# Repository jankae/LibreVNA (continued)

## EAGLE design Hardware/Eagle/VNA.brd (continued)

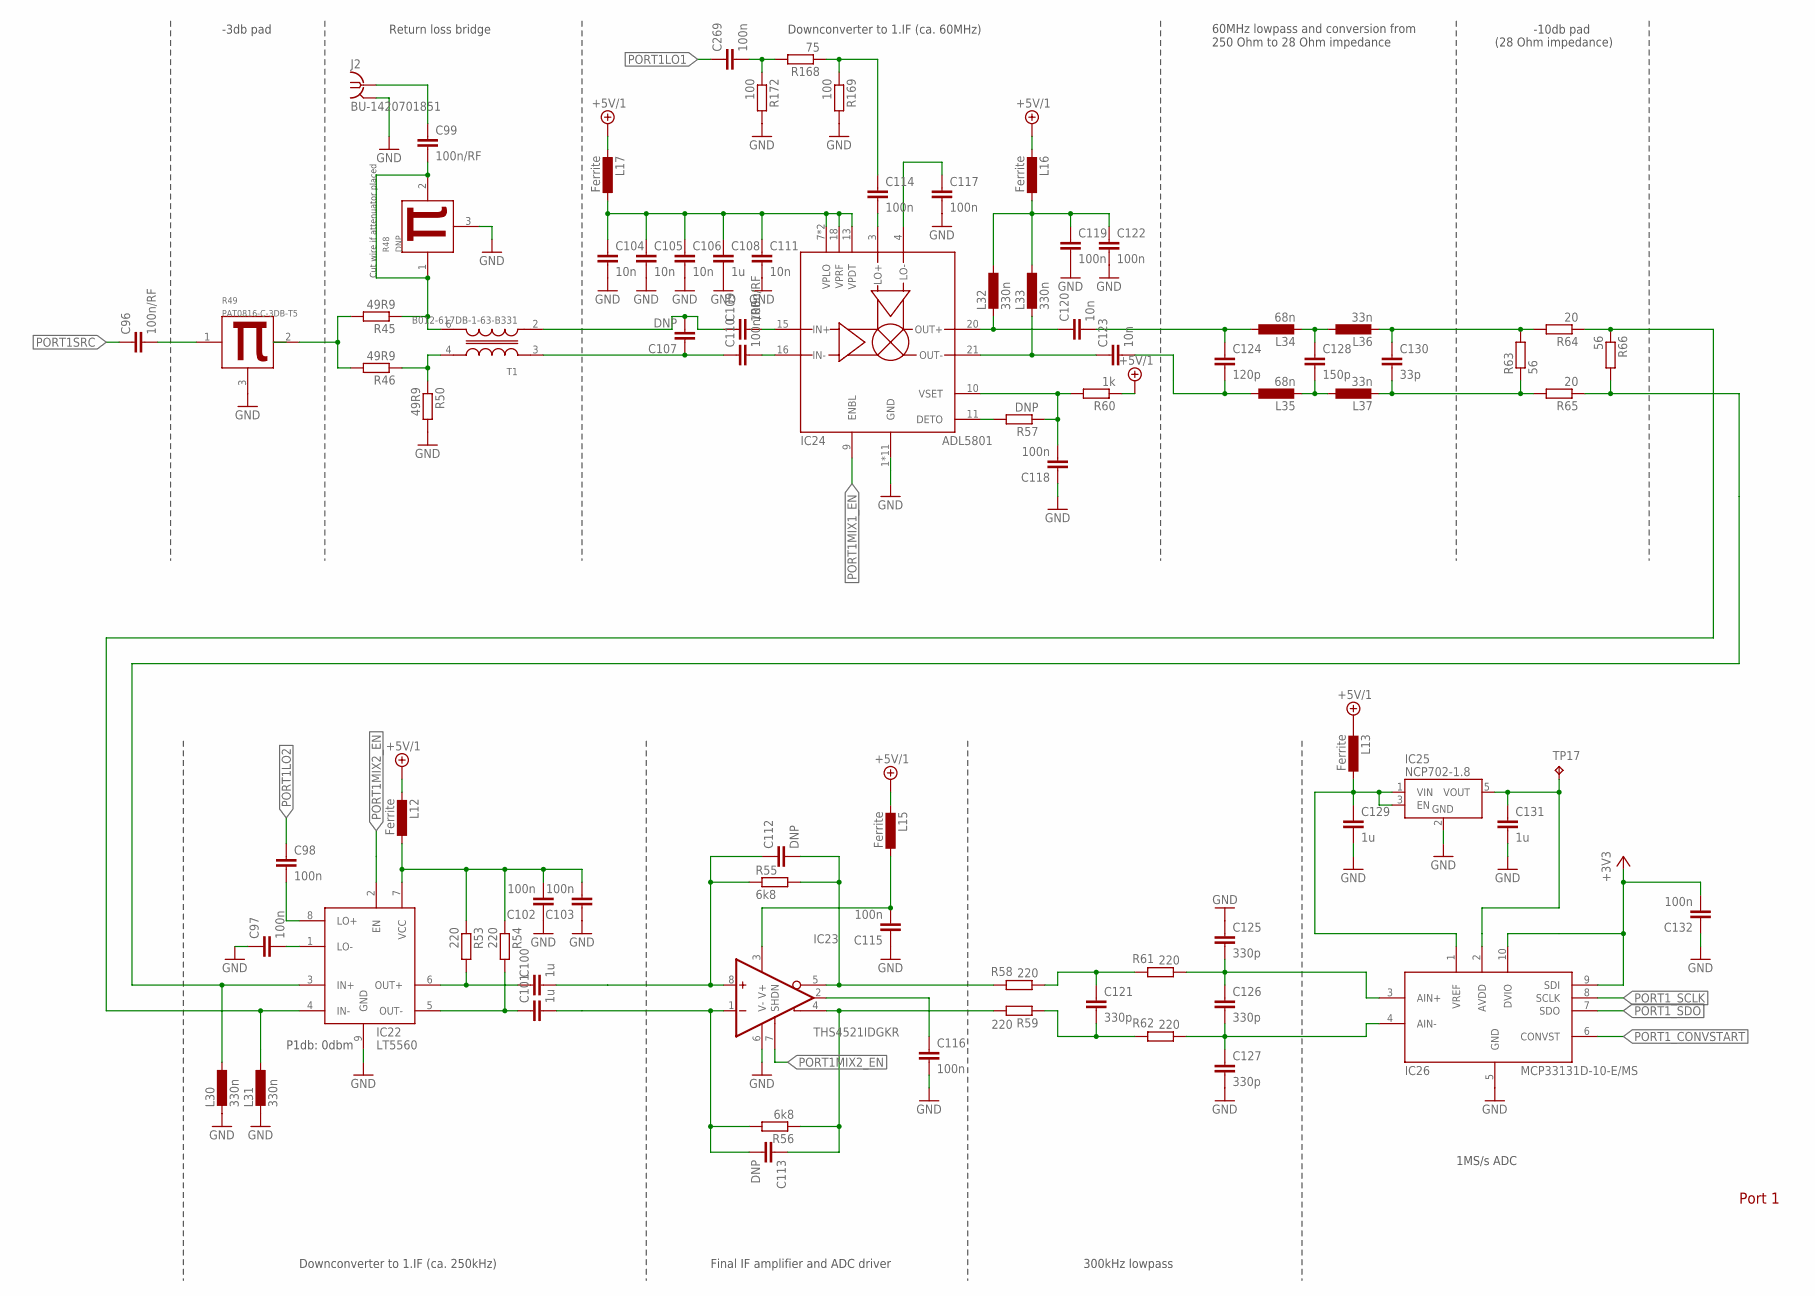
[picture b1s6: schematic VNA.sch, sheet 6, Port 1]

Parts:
C96, C99, C109, C110: 100n/RF; C0402
C97, C98, C102, C103, C114, C115, C116, C117, C118, C119, C122, C132, C269: 100n; C0402
C100, C101, C108, C129, C131: 1u; C0402
C104, C105, C106, C111, C120, C123: 10n; C0402
C107, C112, C113: DNP; C0402
C121, C125, C126, C127: 330p; C0402
C124: 120p; C0402
C128: 150p; C0402
C130: 33p; C0402
IC22: LT5560; SON50P300X300X80-9T165X238
IC23: THS4521IDGKR; SOP65P490X110-8N
IC24: ADL5801; QFN50P400X400X100-25T250N
IC25: NCP702-1.8; SOT95P240X110-5
IC26: MCP33131D-10-E/MS; SOP50P490X110-10N
J2: BU-1420701851
L12, L13, L15, L16, L17: Ferrite; R0402
L30, L31, L32, L33: 330n; L0402
L34, L35: 68n; L0402
L36, L37: 33n; L0402
R45, R46, R50: 49R9; R0402
R48: DNP; PAT0816
R49: PAT0816-C-3DB-T5; PAT0816
R53, R54, R58, R59, R61, R62: 220; R0402
R55, R56: 6k8; R0402
R57: DNP; R0402
R60: 1k; R0402
R63, R66: 56; R0402
R64, R65: 20; R0402
R168: 75; R0402
R169, R172: 100; R0402
T1: B012-617DB-1-63-B331; EASTEVER_BALUN
TP17: TPB1,27; B1,27

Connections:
+3V3: C132.2, IC26.9 (SDI), IC26.10 (DVIO); also elsewhere on the board
+5V/1: L12.2, L13.2, L15.2, L16.2, L17.2, R60.1; also elsewhere on the board
GND: C97.1, C102.1, C103.1, C104.2, C105.2, C106.2, C108.2, C111.2, C115.1, C116.2, C117.2, C118.1, C119.2, C122.2, C125.1, C127.2, C129.2, C131.2, C132.1, IC22.9 (GND), IC23.6 (V-), IC24.1 (GND), IC24.2 (GND), IC24.5 (GND), IC24.6 (GND), IC24.8 (GND), IC24.12 (GND), IC24.14 (GND), IC24.17 (GND), IC24.19 (GND), IC24.23 (GND), IC24.25 (GND), IC25.2 (GND), IC26.5 (GND), J2.G@1 (2), J2.G@2 (2), J2.G@3 (2), J2.G@4 (2), L30.2, L31.2, R48.3 (GND), R49.3 (GND), R50.2, R169.2, R172.2; also elsewhere on the board
unnamed: C96.2, R49.1 (IN)
unnamed: R45.2, R46.2, R49.2 (OUT)
unnamed: C120.2, C124.1, L34.1
unnamed: R46.1, R50.1, T1.4 (OUT+)
unnamed: C99.1, J2.1
unnamed: C109.2, IC24.15 (IN+)
unnamed: C110.2, IC24.16 (IN-)
unnamed: C107.1, C110.1, T1.3 (IN+)
unnamed: C107.2, C109.1, T1.2 (IN-)
unnamed: C117.1, IC24.4 (LO-)
unnamed: C114.2, IC24.3 (LO+)
unnamed: C125.2, C126.1, IC26.3 (AIN+), R61.1
unnamed: C120.1, IC24.20 (OUT+), L32.2
unnamed: C123.1, IC24.21 (OUT-), L33.2
unnamed: C123.2, C124.2, L35.1
unnamed: C128.2, L35.2, L37.1
unnamed: C98.2, IC22.8 (LO+)
unnamed: C118.2, IC24.10 (VSET), R57.1, R60.2
unnamed: C126.2, C127.1, IC26.4 (AIN-), R62.1
unnamed: C97.2, IC22.1 (LO-)
unnamed: C102.2, C103.2, IC22.7 (VCC), L12.1, R53.1, R54.1
unnamed: C100.1, IC22.6 (OUT+), R53.2
unnamed: C101.1, IC22.5 (OUT-), R54.2
unnamed: C113.1, IC23.4 (+OUT), R56.1, R59.2
unnamed: C112.2, IC23.5 (-OUT), R55.2, R58.2
unnamed: C128.1, L34.2, L36.1
unnamed: C130.1, L36.2, R63.2, R64.2
unnamed: C130.2, L37.2, R63.1, R65.2
unnamed: C101.2, C113.2, IC23.1 (-IN), R56.2
unnamed: C100.2, C112.1, IC23.8 (+IN), R55.1
unnamed: C131.1, IC25.5 (VOUT), IC26.2 (AVDD), TP17.TP
unnamed: IC22.4 (IN-), L31.1, R64.1, R66.1
unnamed: IC22.3 (IN+), L30.1, R65.1, R66.2
unnamed: IC24.11 (DETO), R57.2
unnamed: C129.1, IC25.1 (VIN), IC25.3 (EN), IC26.1 (VREF), L13.1
unnamed: C119.1, C122.1, L16.1, L32.1, L33.1
unnamed: C269.2, R168.2, R172.1
unnamed: C114.1, R168.1, R169.1
unnamed: C99.2, R45.1, R48.1 (IN), R48.2 (OUT), T1.6 (OUT-)
unnamed: C115.2, IC23.3 (V+), L15.1
unnamed: C104.1, C105.1, C106.1, C108.1, C111.1, IC24.7 (VPLO), IC24.13 (VPDT), IC24.18 (VPRF), IC24.24 (VPLO), L17.1
OUT+: C121.1, R58.1, R61.2
OUT-: C121.2, R59.1, R62.2
OUT_CM: C116.1, IC23.2 (VOCM)
PORT1LO1: C269.1; also elsewhere on the board
PORT1LO2: C98.1; also elsewhere on the board
PORT1MIX1_EN: IC24.9 (ENBL); also elsewhere on the board
PORT1MIX2_EN: IC22.2 (EN), IC23.7 (SHDN); also elsewhere on the board
PORT1SRC: C96.1; also elsewhere on the board
PORT1_CONVSTART: IC26.6 (CONVST); also elsewhere on the board
PORT1_SCLK: IC26.8 (SCLK); also elsewhere on the board
PORT1_SDO: IC26.7 (SDO); also elsewhere on the board

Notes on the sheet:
P1db: 0dbm
-3db pad
Return loss bridge
Downconverter to 1.IF (ca. 60MHz)
60MHz lowpass and conversion from 250 Ohm to 28 Ohm impedance
-10db pad
(28 Ohm impedance)
Downconverter to 1.IF (ca. 250kHz)
Final IF amplifier and ADC driver
300kHz lowpass
1MS/s ADC
Port 1
Cut wire if attenuator placed

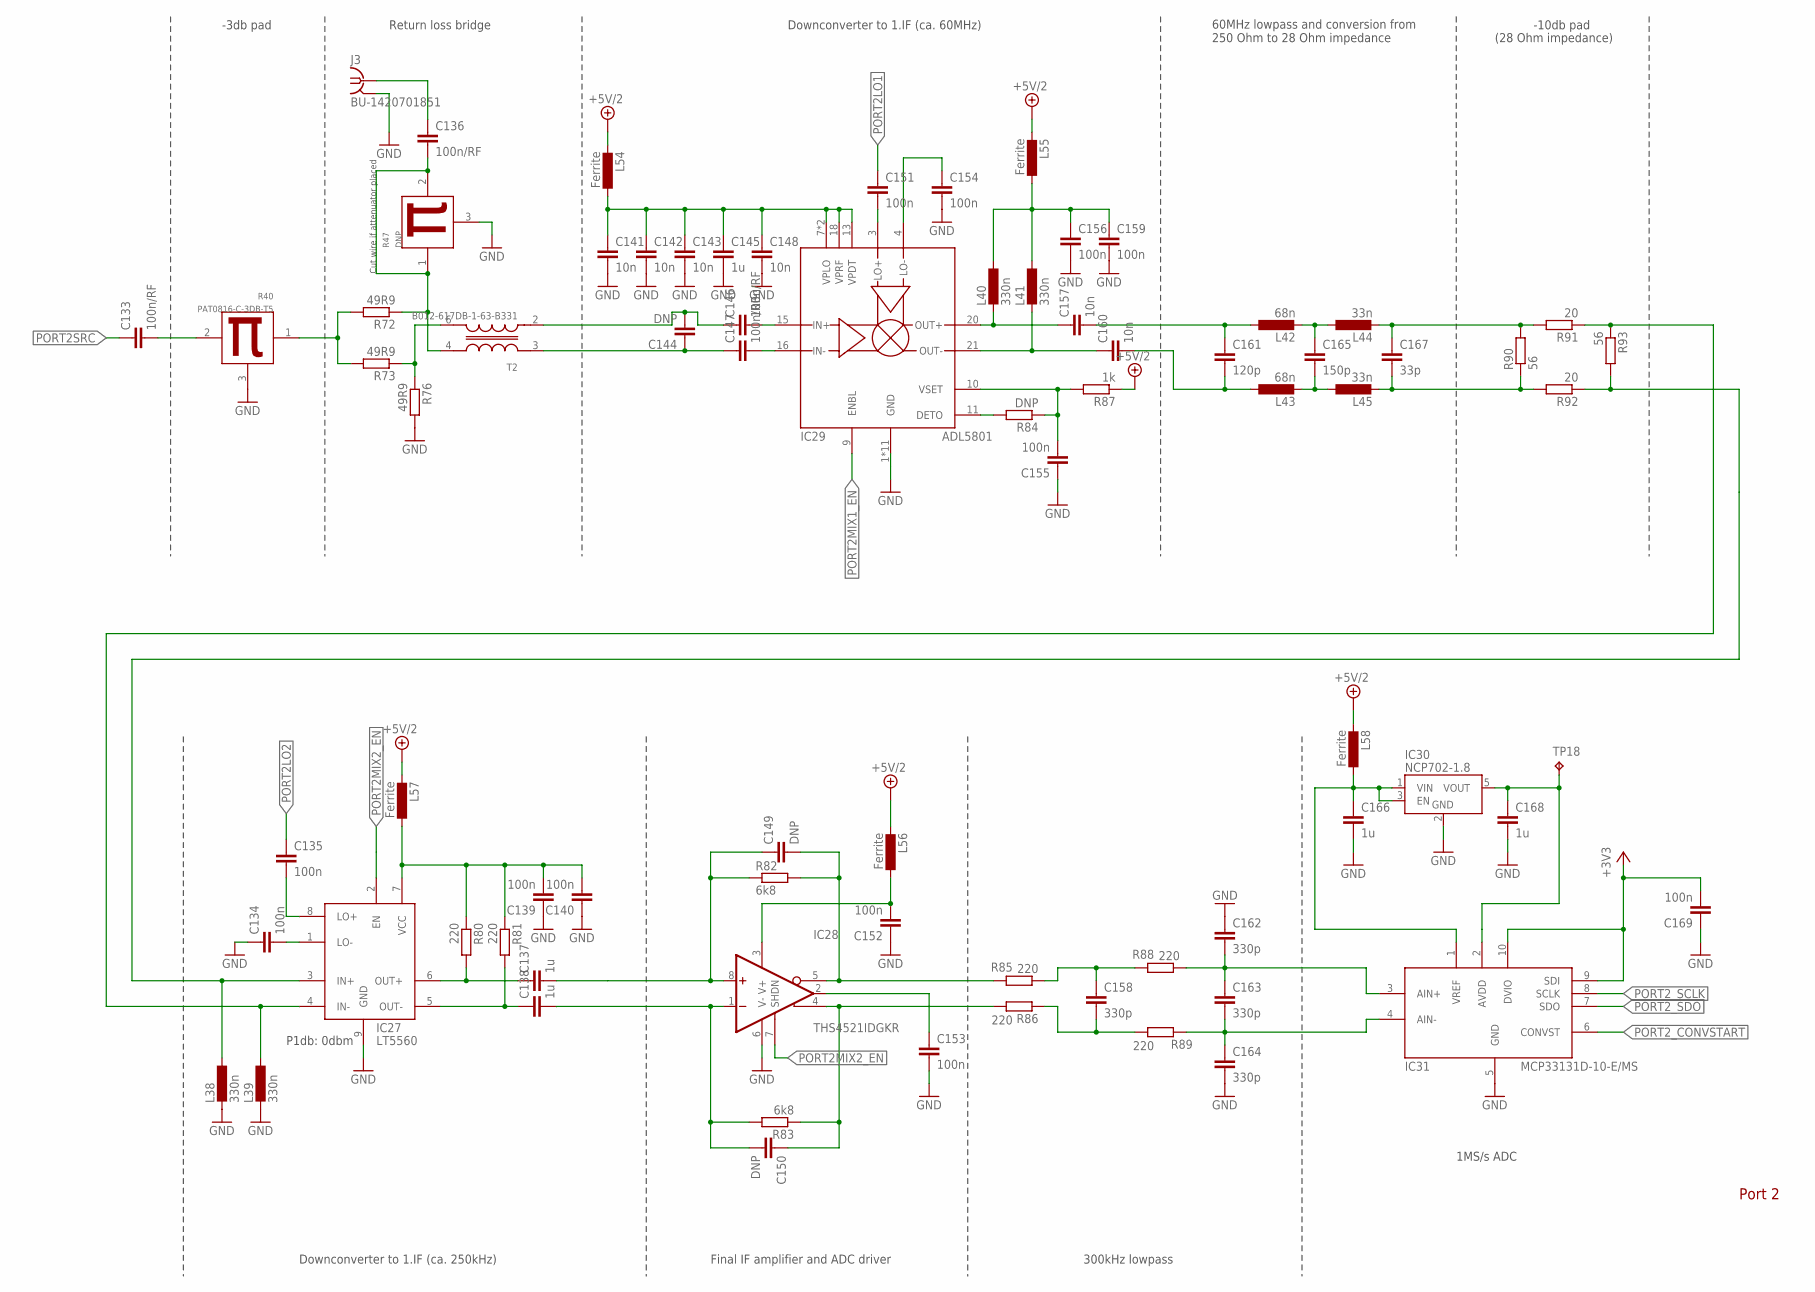
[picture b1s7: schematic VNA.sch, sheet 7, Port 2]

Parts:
C133, C136, C146, C147: 100n/RF; C0402
C134, C135, C139, C140, C151, C152, C153, C154, C155, C156, C159, C169: 100n; C0402
C137, C138, C145, C166, C168: 1u; C0402
C141, C142, C143, C148, C157, C160: 10n; C0402
C144, C149, C150: DNP; C0402
C158, C162, C163, C164: 330p; C0402
C161: 120p; C0402
C165: 150p; C0402
C167: 33p; C0402
IC27: LT5560; SON50P300X300X80-9T165X238
IC28: THS4521IDGKR; SOP65P490X110-8N
IC29: ADL5801; QFN50P400X400X100-25T250N
IC30: NCP702-1.8; SOT95P240X110-5
IC31: MCP33131D-10-E/MS; SOP50P490X110-10N
J3: BU-1420701851
L38, L39, L40, L41: 330n; L0402
L42, L43: 68n; L0402
L44, L45: 33n; L0402
L54, L55, L56, L57, L58: Ferrite; R0402
R40: PAT0816-C-3DB-T5; PAT0816
R47: DNP; PAT0816
R72, R73, R76: 49R9; R0402
R80, R81, R85, R86, R88, R89: 220; R0402
R82, R83: 6k8; R0402
R84: DNP; R0402
R87: 1k; R0402
R90, R93: 56; R0402
R91, R92: 20; R0402
T2: B012-617DB-1-63-B331; EASTEVER_BALUN
TP18: TPB1,27; B1,27

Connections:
+3V3: C169.2, IC31.9 (SDI), IC31.10 (DVIO); also elsewhere on the board
+5V/2: L54.2, L55.2, L56.2, L57.2, L58.2, R87.1; also elsewhere on the board
GND: C134.1, C139.1, C140.1, C141.2, C142.2, C143.2, C145.2, C148.2, C152.1, C153.2, C154.2, C155.1, C156.2, C159.2, C162.1, C164.2, C166.2, C168.2, C169.1, IC27.9 (GND), IC28.6 (V-), IC29.1 (GND), IC29.2 (GND), IC29.5 (GND), IC29.6 (GND), IC29.8 (GND), IC29.12 (GND), IC29.14 (GND), IC29.17 (GND), IC29.19 (GND), IC29.23 (GND), IC29.25 (GND), IC30.2 (GND), IC31.5 (GND), J3.G@1 (2), J3.G@2 (2), J3.G@3 (2), J3.G@4 (2), L38.2, L39.2, R40.3 (GND), R47.3 (GND), R76.2; also elsewhere on the board
unnamed: C136.2, R47.1 (IN), R47.2 (OUT), R72.1, T2.4 (OUT+)
unnamed: C133.2, R40.2 (OUT)
unnamed: R40.1 (IN), R72.2, R73.2
unnamed: IC27.3 (IN+), L38.1, R92.1, R93.2
unnamed: R73.1, R76.1, T2.6 (OUT-)
unnamed: C146.2, IC29.15 (IN+)
unnamed: C147.2, IC29.16 (IN-)
unnamed: C144.1, C147.1, T2.3 (IN+)
unnamed: C144.2, C146.1, T2.2 (IN-)
unnamed: C154.1, IC29.4 (LO-)
unnamed: C151.2, IC29.3 (LO+)
unnamed: C157.1, IC29.20 (OUT+), L40.2
unnamed: C160.1, IC29.21 (OUT-), L41.2
unnamed: C155.2, IC29.10 (VSET), R84.1, R87.2
unnamed: C134.2, IC27.1 (LO-)
unnamed: C137.1, IC27.6 (OUT+), R80.2
unnamed: C138.1, IC27.5 (OUT-), R81.2
unnamed: C150.1, IC28.4 (+OUT), R83.1, R86.2
unnamed: C149.2, IC28.5 (-OUT), R82.2, R85.2
unnamed: C157.2, C161.1, L42.1
unnamed: C160.2, C161.2, L43.1
unnamed: C165.2, L43.2, L45.1
unnamed: C165.1, L42.2, L44.1
unnamed: C135.2, IC27.8 (LO+)
unnamed: C162.2, C163.1, IC31.3 (AIN+), R88.1
unnamed: C163.2, C164.1, IC31.4 (AIN-), R89.1
unnamed: C167.1, L44.2, R90.2, R91.2
unnamed: C167.2, L45.2, R90.1, R92.2
unnamed: C138.2, C150.2, IC28.1 (-IN), R83.2
unnamed: C137.2, C149.1, IC28.8 (+IN), R82.1
unnamed: C168.1, IC30.5 (VOUT), IC31.2 (AVDD), TP18.TP
unnamed: IC27.4 (IN-), L39.1, R91.1, R93.1
unnamed: IC29.11 (DETO), R84.2
unnamed: C136.1, J3.1
unnamed: C141.1, C142.1, C143.1, C145.1, C148.1, IC29.7 (VPLO), IC29.13 (VPDT), IC29.18 (VPRF), IC29.24 (VPLO), L54.1
unnamed: C156.1, C159.1, L40.1, L41.1, L55.1
unnamed: C152.2, IC28.3 (V+), L56.1
unnamed: C139.2, C140.2, IC27.7 (VCC), L57.1, R80.1, R81.1
unnamed: C166.1, IC30.1 (VIN), IC30.3 (EN), IC31.1 (VREF), L58.1
OUT+1: C158.1, R85.1, R88.2
OUT-1: C158.2, R86.1, R89.2
OUT_CM1: C153.1, IC28.2 (VOCM)
PORT2LO1: C151.1; also elsewhere on the board
PORT2LO2: C135.1; also elsewhere on the board
PORT2MIX1_EN: IC29.9 (ENBL); also elsewhere on the board
PORT2MIX2_EN: IC27.2 (EN), IC28.7 (SHDN); also elsewhere on the board
PORT2SRC: C133.1; also elsewhere on the board
PORT2_CONVSTART: IC31.6 (CONVST); also elsewhere on the board
PORT2_SCLK: IC31.8 (SCLK); also elsewhere on the board
PORT2_SDO: IC31.7 (SDO); also elsewhere on the board

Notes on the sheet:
P1db: 0dbm
-3db pad
Return loss bridge
Downconverter to 1.IF (ca. 60MHz)
60MHz lowpass and conversion from 250 Ohm to 28 Ohm impedance
-10db pad
(28 Ohm impedance)
Downconverter to 1.IF (ca. 250kHz)
Final IF amplifier and ADC driver
300kHz lowpass
1MS/s ADC
Port 2
Cut wire if attenuator placed

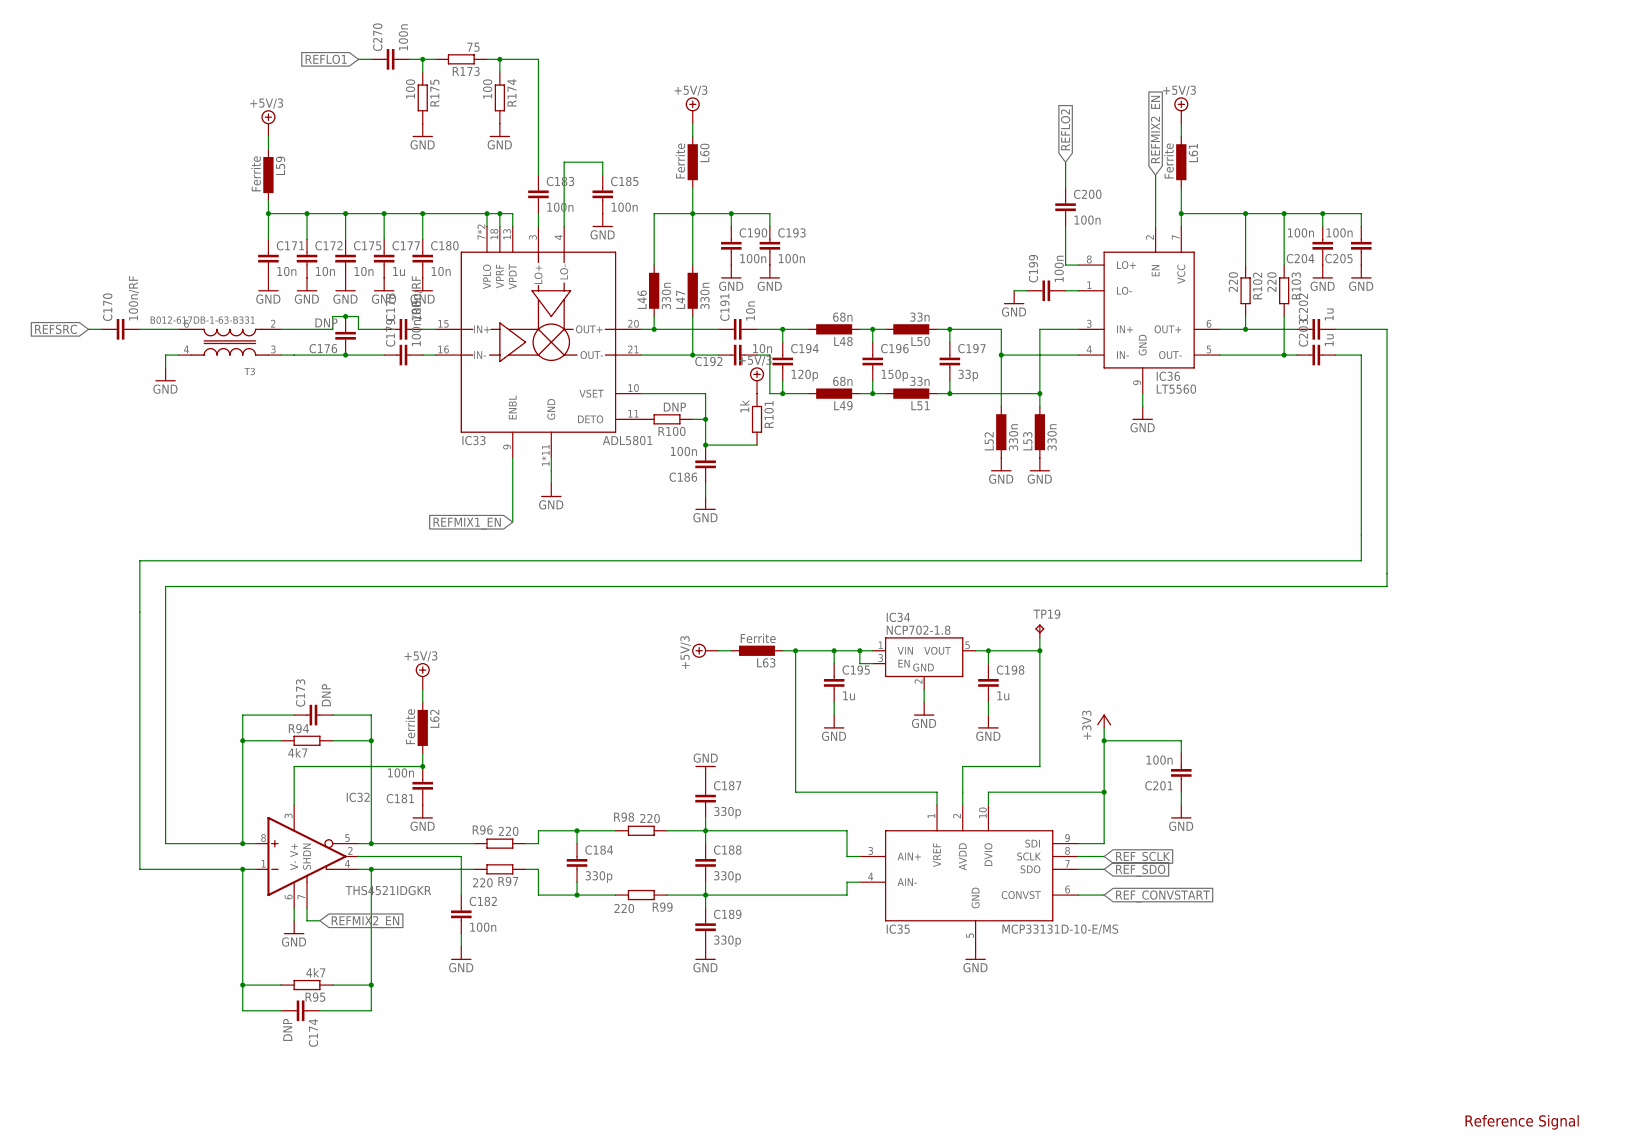
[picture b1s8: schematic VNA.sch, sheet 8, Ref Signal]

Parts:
C170, C178, C179: 100n/RF; C0402
C171, C172, C175, C180, C191, C192: 10n; C0402
C173, C174, C176: DNP; C0402
C177, C195, C198, C202, C203: 1u; C0402
C181, C182, C183, C185, C186, C190, C193, C199, C200, C201, C204, C205, C270: 100n; C0402
C184, C187, C188, C189: 330p; C0402
C194: 120p; C0402
C196: 150p; C0402
C197: 33p; C0402
IC32: THS4521IDGKR; SOP65P490X110-8N
IC33: ADL5801; QFN50P400X400X100-25T250N
IC34: NCP702-1.8; SOT95P240X110-5
IC35: MCP33131D-10-E/MS; SOP50P490X110-10N
IC36: LT5560; SON50P300X300X80-9T165X238
L46, L47, L52, L53: 330n; L0402
L48, L49: 68n; L0402
L50, L51: 33n; L0402
L59, L60, L61, L62, L63: Ferrite; R0402
R94, R95: 4k7; R0402
R96, R97, R98, R99, R102, R103: 220; R0402
R100: DNP; R0402
R101: 1k; R0402
R173: 75; R0402
R174, R175: 100; R0402
T3: B012-617DB-1-63-B331; EASTEVER_BALUN
TP19: TPB1,27; B1,27

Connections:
+3V3: C201.2, IC35.9 (SDI), IC35.10 (DVIO); also elsewhere on the board
+5V/3: L59.2, L60.2, L61.2, L62.2, L63.1, R101.1; also elsewhere on the board
GND: C171.2, C172.2, C175.2, C177.2, C180.2, C181.1, C182.2, C185.2, C186.1, C187.1, C189.2, C190.2, C193.2, C195.2, C198.2, C199.1, C201.1, C204.1, C205.1, IC32.6 (V-), IC33.1 (GND), IC33.2 (GND), IC33.5 (GND), IC33.6 (GND), IC33.8 (GND), IC33.12 (GND), IC33.14 (GND), IC33.17 (GND), IC33.19 (GND), IC33.23 (GND), IC33.25 (GND), IC34.2 (GND), IC35.5 (GND), IC36.9 (GND), L52.2, L53.2, R174.2, R175.2, T3.4 (OUT+); also elsewhere on the board
unnamed: C170.2, T3.6 (OUT-)
unnamed: C178.2, IC33.15 (IN+)
unnamed: C179.2, IC33.16 (IN-)
unnamed: C176.1, C179.1, T3.3 (IN+)
unnamed: C176.2, C178.1, T3.2 (IN-)
unnamed: C185.1, IC33.4 (LO-)
unnamed: C183.2, IC33.3 (LO+)
unnamed: C191.1, IC33.20 (OUT+), L46.2
unnamed: C192.1, IC33.21 (OUT-), L47.2
unnamed: C186.2, IC33.10 (VSET), R100.1, R101.2
unnamed: C199.2, IC36.1 (LO-)
unnamed: C202.1, IC36.6 (OUT+), R102.2
unnamed: C203.1, IC36.5 (OUT-), R103.2
unnamed: C173.1, C202.2, IC32.8 (+IN), R94.1
unnamed: C174.2, C203.2, IC32.1 (-IN), R95.2
unnamed: C174.1, IC32.4 (+OUT), R95.1, R97.2
unnamed: C173.2, IC32.5 (-OUT), R94.2, R96.2
unnamed: C191.2, C194.1, L48.1
unnamed: C192.2, C194.2, L49.1
unnamed: C196.2, L49.2, L51.1
unnamed: C196.1, L48.2, L50.1
unnamed: C197.1, IC36.4 (IN-), L50.2, L52.1
unnamed: C197.2, IC36.3 (IN+), L51.2, L53.1
unnamed: C200.2, IC36.8 (LO+)
unnamed: C187.2, C188.1, IC35.3 (AIN+), R98.1
unnamed: C188.2, C189.1, IC35.4 (AIN-), R99.1
unnamed: C198.1, IC34.5 (VOUT), IC35.2 (AVDD), TP19.TP
unnamed: IC33.11 (DETO), R100.2
unnamed: C270.2, R173.2, R175.1
unnamed: C183.1, R173.1, R174.1
unnamed: C171.1, C172.1, C175.1, C177.1, C180.1, IC33.7 (VPLO), IC33.13 (VPDT), IC33.18 (VPRF), IC33.24 (VPLO), L59.1
unnamed: C190.1, C193.1, L46.1, L47.1, L60.1
unnamed: C204.2, C205.2, IC36.7 (VCC), L61.1, R102.1, R103.1
unnamed: C181.2, IC32.3 (V+), L62.1
unnamed: C195.1, IC34.1 (VIN), IC34.3 (EN), IC35.1 (VREF), L63.2
OUT+2: C184.1, R96.1, R98.2
OUT-2: C184.2, R97.1, R99.2
OUT_CM2: C182.1, IC32.2 (VOCM)
REFLO1: C270.1; also elsewhere on the board
REFLO2: C200.1; also elsewhere on the board
REFMIX1_EN: IC33.9 (ENBL); also elsewhere on the board
REFMIX2_EN: IC32.7 (SHDN), IC36.2 (EN); also elsewhere on the board
REFSRC: C170.1; also elsewhere on the board
REF_CONVSTART: IC35.6 (CONVST); also elsewhere on the board
REF_SCLK: IC35.8 (SCLK); also elsewhere on the board
REF_SDO: IC35.7 (SDO); also elsewhere on the board

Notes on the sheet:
Reference Signal

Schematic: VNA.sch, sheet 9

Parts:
C206, C207, C208, C209, C210, C211, C212, C213, C214, C215, C216, C217, C218, C219, C220, C221, C222: 100n; C0402
C231, C232, C233, C234: 100p; C0402
IC37: STM32G431CB; QFN50P700X700X60-49T560N
J4: TYPE-C16P(073); TYPE-C16P
JP1: DNP; 1X10/90
LED1: Red; CHIPLED_0603
R104, R105, R106, R107, R108, R109, R110: 0; R0402
R111, R112, R113, R114, R115: DNP; R0402
R116, R117, R121, R122, R127, R128, R129, R147, R148: 10k; R0402
R118, R119, R123, R124, R126: 20; R0402
R120: 330; R0402
U1: W25Q16BVSN; SO08
U2: 6SLX9TQG144; TQ144

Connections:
+3V3: C206.1, C207.1, C208.1, C209.1, C210.1, C212.1, C214.1, C216.1, C218.1, C220.1, C221.1, C222.1, IC37.1 (VBAT), IC37.20 (VREF+), IC37.21 (VDDA), IC37.23 (VDD), IC37.35 (VDD), IC37.48 (VDD), JP1.5, LED1.A, R108.1, R116.2, R117.2, R121.2, R127.2, R128.2, R129.2, U1.3 (!WP!), U1.7 (!HOLD!), U1.8 (VCC), U2.P20 (VCCAUX), U2.P36 (VCCAUX), U2.P42 (VCCO_2), U2.P53 (VCCAUX), U2.P63 (VCCO_2), U2.P69 (IO_L1N_M0_CMPMISO_2), U2.P90 (VCCAUX), U2.P129 (VCCAUX); also elsewhere on the board
EN_6V: IC37.25 (PB12); also elsewhere on the board
FPGA_CCLK: R109.2, R111.2, U2.P70 (IO_L1P_CCLK_2)
FPGA_CLK: R126.1; also elsewhere on the board
FPGA_CSO_B: R114.2, U2.P38 (IO_L65N_CSO_B_2)
FPGA_DIN: R110.2, R113.2, U2.P65 (IO_L3P_D0_DIN_MISO_MISO1_2)
FPGA_DONE: IC37.47 (PB9), R129.1, U2.P71 (DONE_2)
FPGA_INIT_B: IC37.6 (PF1-OSC_OUT), R128.1, U2.P39 (IO_L65P_INIT_B_2)
FPGA_M1: R108.2, R115.1, U2.P60 (IO_L13P_M1_2)
FPGA_MOSI: R112.2, U2.P64 (IO_L3N_MOSI_CSI_B_MISO0_2)
FPGA_PROGRAM_B: IC37.19 (PB2), R127.1, U2.P37 (PROGRAM_B_2)
FPGA_RESET: IC37.45 (PB7), U2.P72 (CMPCS_B_2)
GND: C206.2, C207.2, C208.2, C209.2, C210.2, C211.2, C212.2, C213.2, C214.2, C215.2, C216.2, C217.2, C218.2, C219.2, C220.2, C221.2, C222.2, C231.2, C232.2, C233.2, C234.2, IC37.46 (PB8-BOOT0), IC37.49 (GND), J4.1 (GND), J4.12 (GND), J4.M1 (CASE), J4.M2 (CASE), J4.M3 (CASE), J4.M4 (CASE), JP1.7, R115.2, R122.1, U1.4 (GND), U2.P3 (GND), U2.P13 (GND), U2.P25 (GND), U2.P49 (GND), U2.P54 (GND), U2.P68 (GND), U2.P73 (SUSPEND), U2.P77 (GND), U2.P91 (GND), U2.P96 (GND), U2.P108 (GND), U2.P113 (GND), U2.P130 (GND), U2.P136 (GND); also elsewhere on the board
LO1_CE: U2.P45 (IO_L49N_D4_2); also elsewhere on the board
LO1_CLK: U2.P48 (IO_L48P_D7_2); also elsewhere on the board
LO1_LD: U2.P56 (IO_L30P_GCLK1_D13_2); also elsewhere on the board
LO1_LE: U2.P46 (IO_L49P_D3_2); also elsewhere on the board
LO1_MOSI: U2.P47 (IO_L48N_RDWR_B_VREF_2); also elsewhere on the board
LO1_MUX: U2.P51 (IO_L31P_GCLK31_D14_2); also elsewhere on the board
LO1_RF_EN: U2.P55 (IO_L30N_GCLK0_USERCCLK_2); also elsewhere on the board
MCU_AUX1: IC37.9 (PA1); also elsewhere on the board
MCU_AUX2: IC37.10 (PA2); also elsewhere on the board
MCU_AUX3: IC37.11 (PA3); also elsewhere on the board
MCU_FLASH_CS: IC37.17 (PB0), R107.1
MCU_FPGA_CCLK: IC37.26 (PB13), R109.1
MCU_FPGA_DIN: IC37.28 (PB15), R110.1
MCU_FPGA_NSS: IC37.12 (PA4), U2.P67 (IO_L2P_CMPCLK_2)
MCU_FPGA_UNUSED1: IC37.43 (PB5); also elsewhere on the board
MCU_FPGA_UNUSED2: IC37.41 (PB3); also elsewhere on the board
MCU_FPGA_UNUSED3: IC37.40 (PC11); also elsewhere on the board
MCU_INTR: IC37.18 (PB1), U2.P59 (IO_L13N_D10_2)
MCU_MISO: IC37.14 (PA6), R106.1, U2.P62 (IO_L12P_D1_MISO2_2)
MCU_MOSI: IC37.15 (PA7), R105.1, U2.P61 (IO_L12N_D2_MISO3_2)
MCU_SCK: IC37.13 (PA5), R104.1, U2.P66 (IO_L2N_CMPMOSI_2)
unnamed: C232.1, R122.2, R147.1, U2.P57 (IO_L14N_D12_2)
unnamed: J4.6 (D+1), J4.8 (D+2), R119.2
unnamed: IC37.33 (PA11), R118.2
unnamed: IC37.34 (PA12), R119.1
unnamed: J4.5 (D-2), J4.7 (D-1), R118.1
unnamed: LED1.C, R120.1
unnamed: IC37.38 (PA15), R120.2
unnamed: R104.2, R111.1, U1.6 (CLK)
unnamed: R126.2, U2.P50 (IO_L31N_GCLK30_D15_2)
unnamed: R124.2, U2.P41 (IO_L64P_D8_2)
unnamed: R123.2, U2.P43 (IO_L62N_D6_2)
unnamed: IC37.31 (PA9), IC37.44 (PB6), J4.4 (CC1)
unnamed: IC37.32 (PA10), IC37.42 (PB4), J4.10 (CC2)
unnamed: R105.2, R112.1, U1.5 (DI)
unnamed: R106.2, R113.1, U1.2 (DO)
unnamed: R107.2, R114.1, U1.1 (!CS!)
unnamed: C234.1, R121.1, R148.2, U2.P58 (IO_L14P_D11_2)
NRST: IC37.7 (PG10-NRST), JP1.9
PORT2MIX1_EN: C233.1, R148.1; also elsewhere on the board
PORT2MIX2_EN: C231.1, R147.2; also elsewhere on the board
PORT2SWITCH: U2.P40 (IO_L64N_D9_2); also elsewhere on the board
PORT2_CONVSTART: U2.P44 (IO_L62P_D5_2); also elsewhere on the board
PORT2_SCLK: R124.1; also elsewhere on the board
PORT2_SDO: R123.1; also elsewhere on the board
SCL: IC37.16 (PC4), R116.1; also elsewhere on the board
SDA: IC37.30 (PA8), R117.1; also elsewhere on the board
SWCLK: IC37.37 (PA14), JP1.6
SWDIO: IC37.36 (PA13), JP1.8
TCK: JP1.1, U2.P109 (TCK)
TDI: JP1.3, U2.P110 (TDI)
TDO: JP1.2, U2.P106 (TDO)
TMS: JP1.4, U2.P107 (TMS)
UART_TX: IC37.39 (PC10), JP1.10
USB_POWER: J4.2 (VBUS), J4.11 (VBUS); also elsewhere on the board
VCCINT: C211.1, C213.1, C215.1, C217.1, C219.1, U2.P19 (VCCINT), U2.P28 (VCCINT), U2.P52 (VCCINT), U2.P89 (VCCINT), U2.P128 (VCCINT); also elsewhere on the board

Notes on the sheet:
FPGA + MCU Connections
Place resistors for FPGA master configuration
Place resistors for FPGA slave configuration

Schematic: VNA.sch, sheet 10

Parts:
C223, C224, C225, C226, C227, C228, C229, C230: 100p; C0402
JP2: DNP; 2X10
LED2, LED6, LED7, LED8, LED9, LED10: Green; CHIPLED_0603
LED3, LED4, LED5: Red; CHIPLED_0603
R130, R131, R132, R133, R143, R144, R145, R146: 10k; R0402
R134, R135, R136, R137, R138, R139, R140, R141, R142: 330; R0402
U2: 6SLX9TQG144; TQ144

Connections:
+3V3: JP2.1, LED2.A, LED3.A, LED4.A, LED5.A, LED6.A, LED7.A, LED8.A, LED9.A, LED10.A, R130.2, R132.2, U2.P4 (VCCO_3), U2.P18 (VCCO_3), U2.P31 (VCCO_3), U2.P76 (VCCO_1), U2.P86 (VCCO_1), U2.P103 (VCCO_1), U2.P122 (VCCO_0), U2.P125 (VCCO_0), U2.P135 (VCCO_0); also elsewhere on the board
AMP_PWDN: U2.P8 (IO_L51P_3); also elsewhere on the board
ATT_D0: U2.P16 (IO_L43N_GCLK22_IRDY2_3); also elsewhere on the board
ATT_D1: U2.P15 (IO_L44P_GCLK21_3); also elsewhere on the board
ATT_D2: U2.P14 (IO_L44N_GCLK20_3); also elsewhere on the board
ATT_D3: U2.P12 (IO_L49P_3); also elsewhere on the board
ATT_D4: U2.P11 (IO_L49N_3); also elsewhere on the board
ATT_D5: U2.P10 (IO_L50P_3); also elsewhere on the board
ATT_D6: U2.P9 (IO_L50N_3); also elsewhere on the board
FILT_IN_C1: U2.P26 (IO_L37N_3); also elsewhere on the board
FILT_IN_C2: U2.P24 (IO_L41P_GCLK27_3); also elsewhere on the board
FILT_OUT_C1: U2.P22 (IO_L42P_GCLK25_TRDY2_3); also elsewhere on the board
FILT_OUT_C2: U2.P23 (IO_L41N_GCLK26_3); also elsewhere on the board
GND: C223.2, C224.2, C225.2, C226.2, C227.2, C228.2, C229.2, C230.2, JP2.20, R131.1, R133.1, R134.2; also elsewhere on the board
HIGHBAND_SELECT: U2.P21 (IO_L42N_GCLK24_3); also elsewhere on the board
LOWBAND_SELECT: U2.P17 (IO_L43P_GCLK23_3); also elsewhere on the board
MCU_AUX1: U2.P78 (IO_L47N_1); also elsewhere on the board
MCU_AUX2: U2.P74 (IO_L74N_DOUT_BUSY_1); also elsewhere on the board
MCU_AUX3: U2.P75 (IO_L74P_AWAKE_1); also elsewhere on the board
MCU_FPGA_UNUSED1: U2.P79 (IO_L47P_1); also elsewhere on the board
MCU_FPGA_UNUSED2: U2.P80 (IO_L46N_1); also elsewhere on the board
MCU_FPGA_UNUSED3: U2.P81 (IO_L46P_1); also elsewhere on the board
unnamed: C225.1, R132.1, R144.1, U2.P144 (IO_L1P_HSWAPEN_0)
unnamed: C227.1, R131.2, R145.2, U2.P140 (IO_L3P_0)
unnamed: C229.1, R130.1, R146.1, U2.P141 (IO_L2N_0)
unnamed: R135.2, U2.P92 (IO_L41N_GCLK8_1)
unnamed: R136.2, U2.P93 (IO_L41P_GCLK9_IRDY1_1)
unnamed: JP2.2, U2.P134 (IO_L34P_GCLK19_0)
unnamed: JP2.4, U2.P133 (IO_L34N_GCLK18_0)
unnamed: JP2.3, U2.P132 (IO_L35P_GCLK17_0)
unnamed: LED10.C, R142.1
unnamed: LED9.C, R141.1
unnamed: LED8.C, R140.1
unnamed: LED7.C, R139.1
unnamed: LED6.C, R138.1
unnamed: LED5.C, R137.1
unnamed: LED4.C, R136.1
unnamed: LED3.C, R135.1
unnamed: LED2.C, R134.1
unnamed: R142.2, U2.P82 (IO_L45N_1)
unnamed: R141.2, U2.P83 (IO_L45P_1)
unnamed: R140.2, U2.P84 (IO_L43N_GCLK4_1)
unnamed: R139.2, U2.P85 (IO_L43P_GCLK5_1)
unnamed: R138.2, U2.P87 (IO_L42N_GCLK6_TRDY1_1)
unnamed: R137.2, U2.P88 (IO_L42P_GCLK7_1)
unnamed: JP2.6, U2.P131 (IO_L35N_GCLK16_0)
unnamed: JP2.5, U2.P127 (IO_L36P_GCLK15_0)
unnamed: JP2.8, U2.P126 (IO_L36N_GCLK14_0)
unnamed: JP2.7, U2.P124 (IO_L37P_GCLK13_0)
unnamed: JP2.10, U2.P123 (IO_L37N_GCLK12_0)
unnamed: JP2.9, U2.P121 (IO_L62P_0)
unnamed: JP2.12, U2.P120 (IO_L62N_VREF_0)
unnamed: JP2.11, U2.P119 (IO_L63P_SCP7_0)
unnamed: JP2.14, U2.P118 (IO_L63N_SCP6_0)
unnamed: JP2.13, U2.P117 (IO_L64P_SCP5_0)
unnamed: JP2.16, U2.P116 (IO_L64N_SCP4_0)
unnamed: JP2.15, U2.P115 (IO_L65P_SCP3_0)
unnamed: JP2.18, U2.P114 (IO_L65N_SCP2_0)
unnamed: JP2.17, U2.P112 (IO_L66P_SCP1_0)
unnamed: JP2.19, U2.P111 (IO_L66N_SCP0_0)
unnamed: C223.1, R133.2, R143.2, U2.P143 (IO_L1N_VREF_0)
PORT1MIX1_EN: C230.1, R146.2; also elsewhere on the board
PORT1MIX2_EN: C228.1, R145.1; also elsewhere on the board
PORT1SWITCH: U2.P142 (IO_L2P_0); also elsewhere on the board
PORT1_CONVSTART: U2.P139 (IO_L3N_0); also elsewhere on the board
PORT1_SCLK: U2.P137 (IO_L4N_0); also elsewhere on the board
PORT1_SDO: U2.P138 (IO_L4P_0); also elsewhere on the board
PORTSWITCH1: U2.P6 (IO_L52P_3); also elsewhere on the board
PORTSWITCH2: U2.P7 (IO_L51N_3); also elsewhere on the board
REFMIX1_EN: C226.1, R144.2; also elsewhere on the board
REFMIX2_EN: C224.1, R143.1; also elsewhere on the board
REF_CONVSTART: U2.P5 (IO_L52N_3); also elsewhere on the board
REF_SCLK: U2.P1 (IO_L83N_VREF_3); also elsewhere on the board
REF_SDO: U2.P2 (IO_L83P_3); also elsewhere on the board
SOURCE_CE: U2.P27 (IO_L37P_3); also elsewhere on the board
SOURCE_CLK: U2.P32 (IO_L2N_3); also elsewhere on the board
SOURCE_LD: U2.P35 (IO_L1P_3); also elsewhere on the board
SOURCE_LE: U2.P29 (IO_L36N_3); also elsewhere on the board
SOURCE_MOSI: U2.P30 (IO_L36P_3); also elsewhere on the board
SOURCE_MUX: U2.P33 (IO_L2P_3); also elsewhere on the board
SOURCE_RF_EN: U2.P34 (IO_L1N_VREF_3); also elsewhere on the board

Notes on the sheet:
FPGA Connections

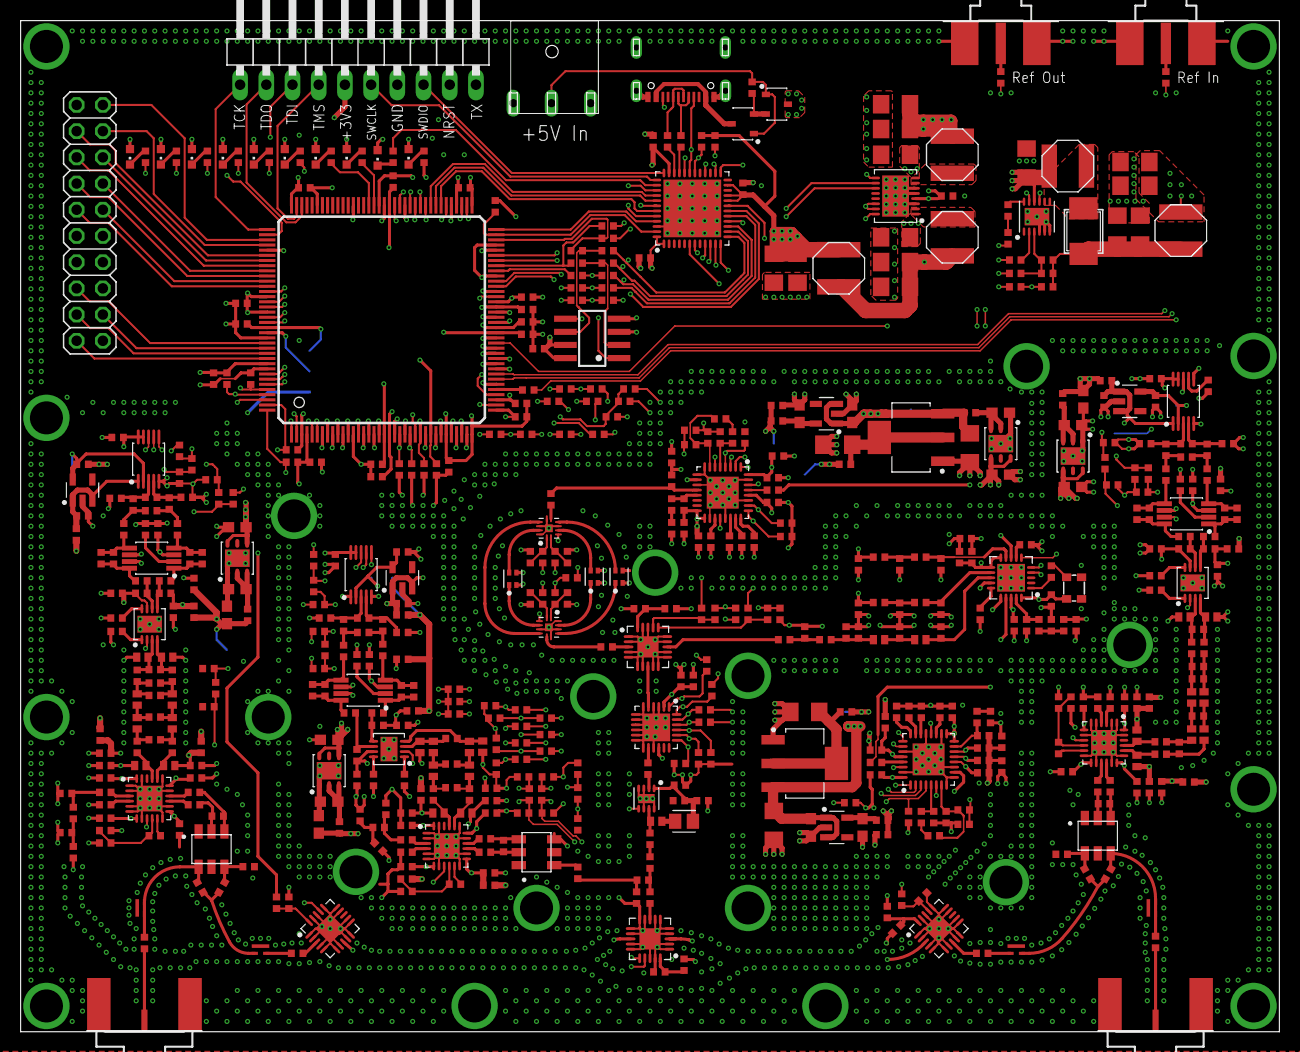
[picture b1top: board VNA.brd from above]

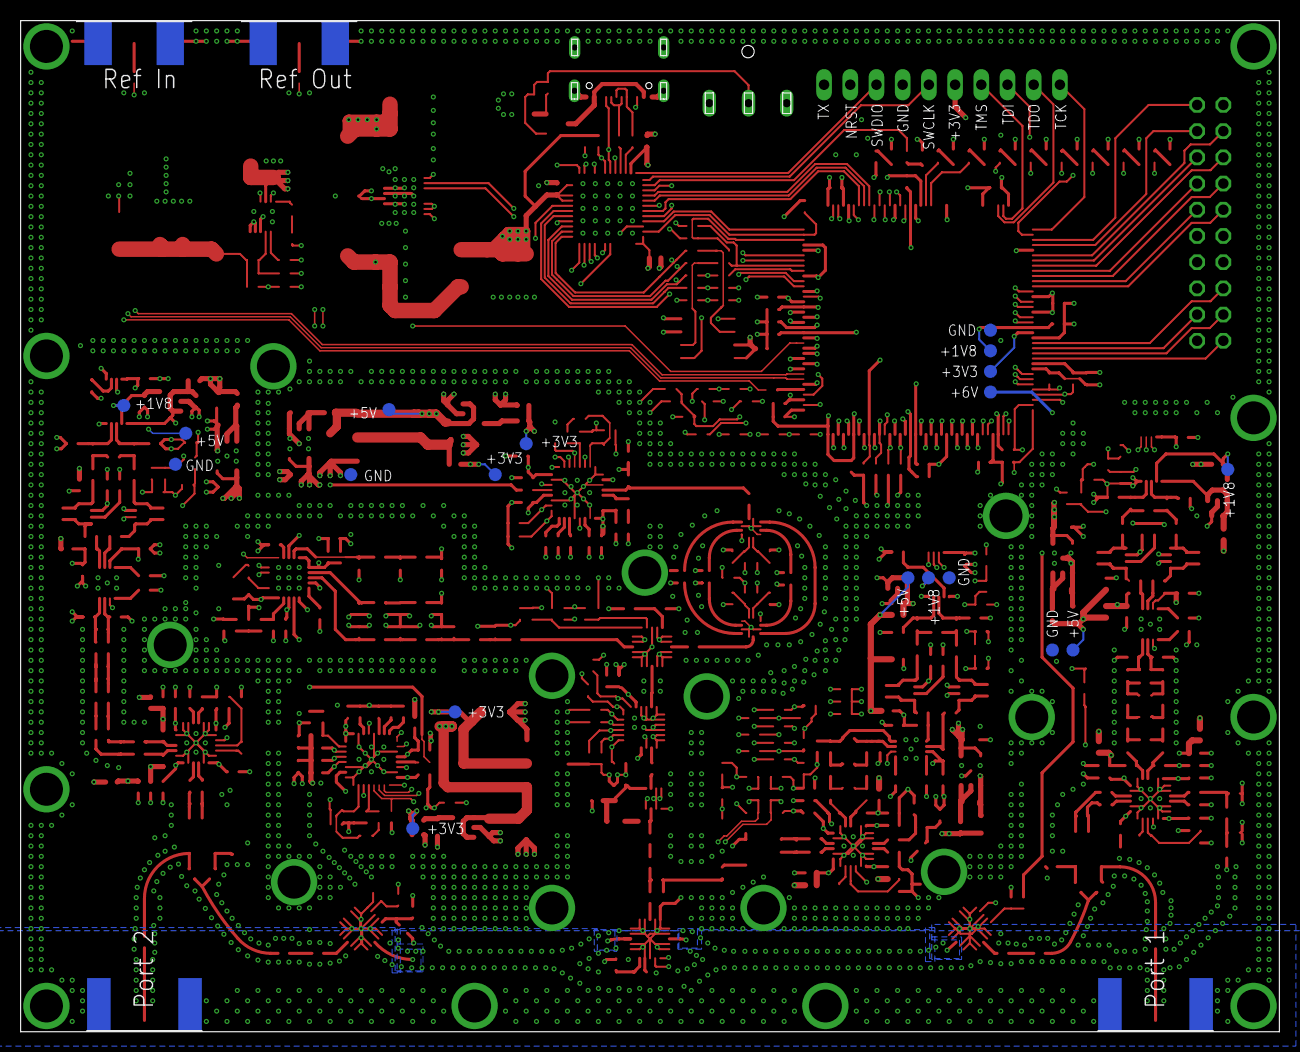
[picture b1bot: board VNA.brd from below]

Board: 6 copper layers, 122.0 x 98.0 mm, 590 parts (19 on the bottom side), 402 nets.
